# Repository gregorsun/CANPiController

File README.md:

# CANPiController

**CAN** **Pi**c **Controller** a CAN 2.0 B or CAN FD Controller board with the [PIC18F27Q84](https://www.microchip.com/wwwproducts/en/PIC18F27Q84) controller and the [ATA65620](https://www.microchip.com/wwwproducts/en/ATA6560) CAN Transeiver.

This example project showcases the setup and use of the new CAN FD module in CAN 2.0 mode on the PIC18-Q84 family of devices with the CANPiController board.The code periodically transmits CAN frames on a 1 second interval until receiving a specific message (modeled after OBD II), then will respond to certain queries with built-in data.
These examples is the CAN implementation of the CAN FD example of [pic18F57q84-curiosity-nano-CAN-node-mplab-mcc](https://github.com/microchip-pic-avr-examples/pic18F57q84-curiosity-nano-CAN-node-mplab-mcc) from @MicrochipTech

## Related Documentation

- Basic Configuration of the CAN FD Module Technical Brief [(ww1.microchip.com/downloads/en/Appnotes/90003266A.pdf)](https://ww1.microchip.com/downloads/en/Appnotes/90003266A.pdf)
- PIC18F27/47/57Q84 Datasheet [(https://www.microchip.com/wwwproducts/en/PIC18F57Q84)](https://www.microchip.com/wwwproducts/en/PIC18F57Q84)

## Software Used

- MPLAB® X IDE 5.50 or newer [(microchip.com/mplab/mplab-x-ide)](http://www.microchip.com/mplab/mplab-x-ide)
- MPLAB® XC8 2.32 or a newer compiler [(microchip.com/mplab/compilers)](http://www.microchip.com/mplab/compilers)
- MPLAB® Code Configurator (MCC) 3.95.0 or newer [(microchip.com/mplab/mplab-code-configurator)](https://www.microchip.com/mplab/mplab-code-configurator)
- MPLAB® Code Configurator (MCC) Device Libraries PIC10 / PIC12 / PIC16 / PIC18 MCUs 1.81.7 or newer [(microchip.com/mplab/mplab-code-configurator)](https://www.microchip.com/mplab/mplab-code-configurator)
- Microchip PIC18F-Q Series Device Support (1.11.185) or newer [(packs.download.microchip.com/)](https://packs.download.microchip.com/)

## Hardware Used

Hardware Used

- [*KiCAD* project files](https://github.com/gregorsun/CANPiController/tree/main/KiCAD)
- [README](https://github.com/gregorsun/CANPiController/blob/main/KiCAD/README.md) for the CANPiController PCB board

## Setup

The CANPiController Board is used as the development platform. In addition the [CAN BUS analyzer](https://www.microchip.com/developmenttools/productdetails/apgdt002) or any other CAN bus capable analyzer is needed to view the outgoing CAN frames and send incoming CAN frames to the device.

PIN Setup

PIN Manager Grid View

Other Setup is versy similar to the [pic18F57q84-curiosity-nano-CAN-node-mplab-mcc](https://github.com/microchip-pic-avr-examples/pic18F57q84-curiosity-nano-CAN-node-mplab-mcc)

## Changes to the Setup from the CAN FD demo

Main.c
```c

 //enable CAN Transceiver
 NSIL_SetLow();
 STBY_SetLow();
    
```

created interrupt_handler_function.h to put Interrupt handler to a seperate file
```c
/* 
 * File:   interrupt_handler_function.h
 * Author: M43998
 *
 * Created on July 1, 2021, 11:58 AM
 */

#ifndef INTERRUPT_HANDLER_FUNCTION_H
#define	INTERRUPT_HANDLER_FUNCTION_H

#ifdef	__cplusplus
extern "C" {
#endif

void TU16A__C1_TransmitInterruptHandler(void);
void C1__ReceiveFIFO1NotEmptyHandler(void);

#ifdef	__cplusplus
}
#endif

#endif	/* INTERRUPT_HANDLER_FUNCTION_H */
```

interrupt_handler_function.c
- The Universal timer is used for a 1 second "heartbeat" periodic transmission to ensure that the hardware is properly connected and programmed.  This periodic transmission's code is within the Universal Timer 1A's interrupt routine:
- The CAN is set up to interrupt when the receive FIFO is not empty.  The logic for processing and handling incoming messages is placed within this interrupt.
- The CAN_MSG_OBJ has to be set up as CAN message and not as a CAN FD message!

```c
/**
 Interrupt Handler function

  @author
 * Gregor Sunderdiek

  @File Name
    interrupt_handler_function.c

  @Summary
    Interrupt function handler for CAn and TU16a, so that MCC does not overide the DefaultInterruptHandler in the tu16a.c
 * TU16A_DefaultInterruptHandler has to be disabled in tu16a.c
 
 change in tua16.c
 * // Set Default Interrupt Handler
    TU16A_SetInterruptHandler(TU16A_C1_TransmitInterruptHandler);
 changes in can1.
 * //CAN1_SetFIFO1NotEmptyHandler(DefaultFIFO1NotEmptyHandler);
    CAN1_SetFIFO1NotEmptyHandler(C1__ReceiveFIFO1NotEmptyHandler);
 * 
*/

#include <xc.h>
#include "interrupt_handler_function.h"
#include "mcc_generated_files/can1.h"
#include "mcc_generated_files/tu16a.h"

void TU16A__C1_TransmitInterruptHandler(void){
    CAN_MSG_OBJ Transmission;
    uint8_t Transmit_Data[8]={0x00,0x11,0x22,0x33,0x44,0x55,0x66,0x77};
    __debug_break();
    Transmission.field.brs=CAN_NON_BRS_MODE;
    Transmission.field.dlc=DLC_8;
    Transmission.field.formatType=CAN_2_0_FORMAT;
    Transmission.field.frameType=CAN_FRAME_DATA;
    Transmission.field.idType=CAN_FRAME_STD;
    Transmission.msgId=0x585;
    Transmission.data=Transmit_Data;
    if(CAN_TX_FIFO_AVAILABLE == (CAN1_TransmitFIFOStatusGet(TXQ) & CAN_TX_FIFO_AVAILABLE))
                {
                    CAN1_Transmit(TXQ, &Transmission);
                }
} // end void TU16A_DefaultInterruptHandler(void)

void C1__ReceiveFIFO1NotEmptyHandler(void){
    TU16ACON0bits.ON = 0;  //stop the periodic heartbeat, go into response mode
    CAN_MSG_OBJ Currently_Processing;
    CAN_MSG_OBJ Return_Message;
    uint8_t data_Out[8];
    uint8_t mode=0;
    uint8_t PID=0;
    uint8_t numBytes=0;
    while(1)
    {
        if(CAN1_ReceivedMessageCountGet() > 0) 
        {
            if(true == CAN1_ReceiveFrom(FIFO1,&Currently_Processing)) //receive the message
            {
                break;
            }
        }
    }
    numBytes=Currently_Processing.data[0];
    mode=Currently_Processing.data[1];
    PID=Currently_Processing.data[2];
    Return_Message.msgId=0x7E;
    Return_Message.field.dlc=8;
    Return_Message.field.brs=CAN_NON_BRS_MODE;
    Return_Message.field.idType=CAN_FRAME_STD;
    Return_Message.field.formatType=CAN_2_0_FORMAT;
    Return_Message.field.frameType=CAN_FRAME_DATA;
    data_Out[1]=mode+0x40;
    data_Out[2]=PID;
    data_Out[7]=0x55; //00h or 55h recommended by SAE standard
    if (mode!=0x01||numBytes!=2)  //only respond with current data and a SAE standard broadcast request with 2 following bytes
    {
        return;
    }
    
    else if (PID==0x00)  //PIDs supported
    {
        data_Out[0]=6;
        data_Out[3]=0x18;  //supports engine load, coolant temp
        data_Out[4]=0x78;  //supports fuel pressure, intake pressure, engine speed, vehicle speed
        data_Out[5]=0x00;
        data_Out[6]=0x00;  //no more supported PIDs
        
    }
    
    else if (PID==0x04) //Engine Load
    {
        data_Out[0]=3;
        data_Out[3]=191; //~75% engine load
        data_Out[4]=0x55;  
        data_Out[5]=0x55;
        data_Out[6]=0x55;  
    }

    else if (PID==0x05) //Coolant Temp
    {
        data_Out[0]=3;
        data_Out[3]=100; //60C
        data_Out[4]=0x55;  
        data_Out[5]=0x55;
        data_Out[6]=0x55; 
    }
    
    else if (PID==0x0A) //Fuel Pressure
    {
        data_Out[0]=3;
        data_Out[3]=150; //450 kPA
        data_Out[4]=0x55;  
        data_Out[5]=0x55;
        data_Out[6]=0x55; 
    }
    
    else if (PID==0x0B) //Intake Pressure
    {
        data_Out[0]=3;
        data_Out[3]=200; //200 kPA
        data_Out[4]=0x55;  
        data_Out[5]=0x55;
        data_Out[6]=0x55; 
    }
    
    else if (PID==0x0C) //Engine Speed
    {
        data_Out[0]=4;
        data_Out[3]=54;    //256A+B/4=3500 RPM
        data_Out[4]=176; 
        data_Out[5]=0x55;
        data_Out[6]=0x55; 
    }
    
    else if (PID==0x0D) //Vehicle Speed
    {
        data_Out[0]=3;
        data_Out[3]=70;  //70 km/h
        data_Out[4]=0x55;  
        data_Out[5]=0x55;
        data_Out[6]=0x55; 
    }
    
    else if (PID==0xFF) //go back to heartbeat mode
    {
        TU16ACON0bits.ON = 1;  //stop the response mode, go into periodic heartbeat
        return;
    }
        Return_Message.data=data_Out; 
        if(CAN_TX_FIFO_AVAILABLE == (CAN1_TransmitFIFOStatusGet(TXQ) & CAN_TX_FIFO_AVAILABLE))
        {
            CAN1_Transmit(TXQ, &Return_Message);
        }
        return;

} // end 
```

## Operation

On Power-up, the code will periodically transmit messages 

However, upon receiving a message with the CAN ID of 0x7DF, it will cease the periodic messages and go into response mode.  In this mode it will respond to specific messages, as shown below:

After sending a message with 0xFF in the third data byte while in response mode, the node will return to periodic mode and begin sending periodic messages again.

## Summary

This Demo gives an example of hardware and software setup for a basic CAN node with both periodic and response-driven transmissions, showcasing baud rate setup, message filtering, and RX and TX setup.  

##Debug with MLPAB PICkit4

The PCB connector J3 has not the same connection as the [PICkit4 Debugger](https://www.microchip.com/DevelopmentTools/ProductDetails/PartNO/PG164140)

A cable with soldering with connector is needed to match the PICkit4

with the CANPiController board ICSP Interface J3

PICkit4 Header
| PICkit4       |
| ------------- | 
| 1. VPP/MCLR   |
| 2. VDD        |
| 3. VSS        | 
| 4. PGD        | 
| 5. PGC        | 
| 6. NC         | 

ICSP Header J3 on the CANPIController
| ICSP J3       |
| ------------- |
| 1. MCLR VPP   |
| 2. +5V VDD    |
| 3. ICSPDAT    |
| 4. ICSPCLK    |
| 5. NC         |
| 6. GND        |

Connection from the PICkit4 Header to the ICSP Header J3 on the CANPIController
| PICkit4       | ICSP J3       |
| ------------- | ------------- |
| 1. VPP/MCLR   | 1. MCLR VPP   |
| 2. VDD        | 2. +5V VDD    |
| 3. VSS        | 6. GND        |
| 4. PGD        | 3. ICSPDAT    |
| 5. PGC        | 5. NC         |
| 6. NC         | 4. ICSPCLK    |

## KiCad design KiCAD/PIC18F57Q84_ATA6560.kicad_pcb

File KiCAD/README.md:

**KiCAD project file for the CANPicontroller ver1**
*Main components*
1. Semiconductors
  - U1 - [PIC18F27Q84-ISS](https://www.microchip.com/wwwproducts/en/PIC18F27Q84) for CAN-FD or [PIC18F27Q83-ISS](https://www.microchip.com/wwwproducts/en/PIC18F27Q83) for CAN 2.0V 
  - U2 - CAN Transceiver - [ATA6560](https://www.microchip.com/wwwproducts/en/ATA6560)
2. Electromechanical
  - J1 - USB-C for +5V only
  - J2 - Header for USB-C
  - J3 - [ICSP-Header](https://ww1.microchip.com/downloads/en/devicedoc/30277d.pdf)
  - J4 - Header for signals CANH, CANL and GND
  - J5 and J6 Header - Curiosity Nano Debug Header
    - You have to use a [PIC18F57Q84 Curiosity Nano](https://ww1.microchip.com/downloads/en/DeviceDoc/PIC18F57Q84-Curiosity-Nano-Hardware-User-Guide-DS50003011.pdf)
    - Only the  Curiosity Nano Standard Pinout Pins are needed
    - 
  - J7 Header - signal to/from CAN Transceiver
  - J8 and J9 - [Mikroelektonika click header](https://www.mikroe.com/click-boards)
  - J10 - DB9 male connector for CAN connection

*WARNING*
- Only connect one power supply to the board, Either power the board via USB, the ICSP header or the PIC18F-Q84 Curiosity Nano header

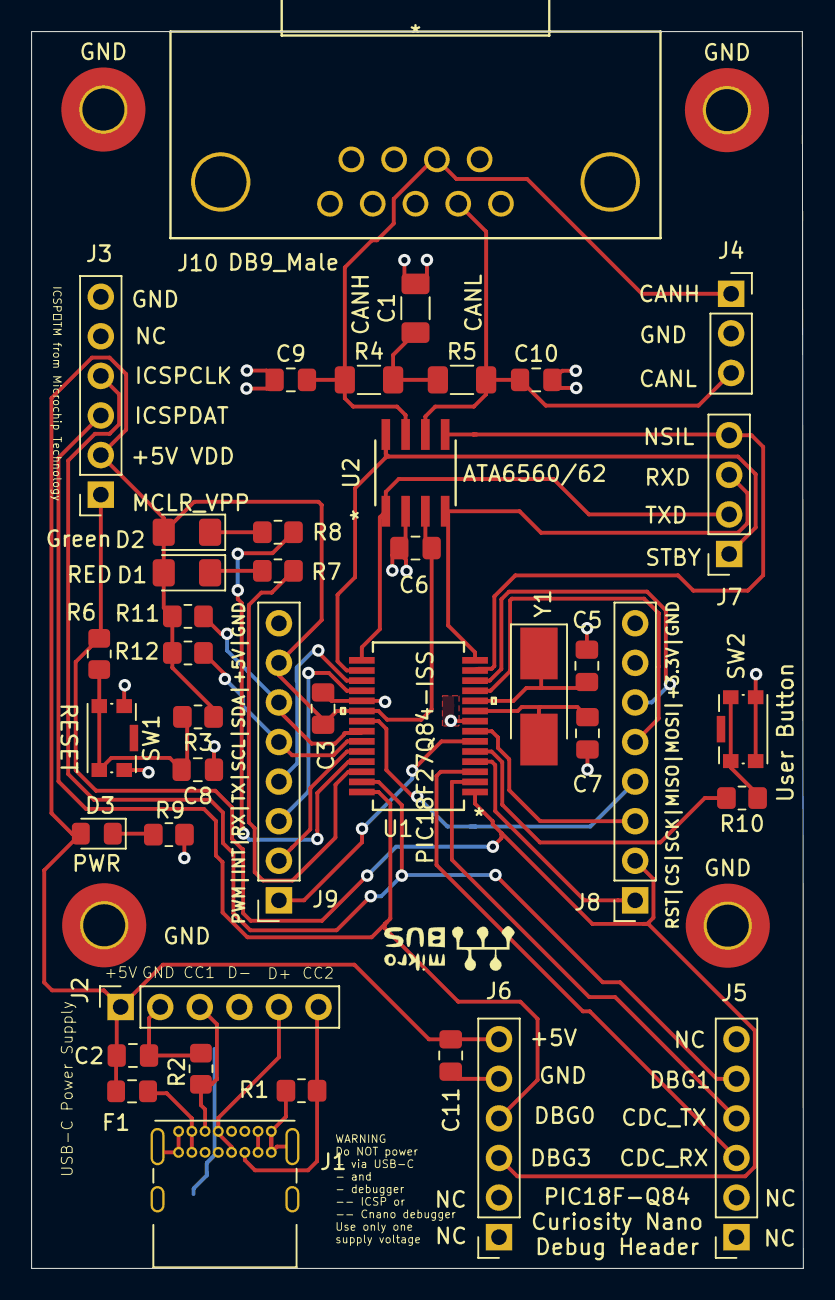
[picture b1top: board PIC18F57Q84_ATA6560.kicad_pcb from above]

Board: 2 copper layers, 49.5 x 79.4 mm, 45 parts (0 on the bottom side), 40 nets.

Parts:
C1: 4.7n/50V; C_1206_3216Metric_Pad1.33x1.80mm_HandSolder
C2, C11: 2.2u; C_0805_2012Metric_Pad1.18x1.45mm_HandSolder
C3, C6: 100n; C_0805_2012Metric_Pad1.18x1.45mm_HandSolder
C5, C7: 26p; C_0805_2012Metric_Pad1.18x1.45mm_HandSolder
C8: 0.1u; C_0805_2012Metric_Pad1.18x1.45mm_HandSolder
C9, C10: 100p/50V; C_0805_2012Metric_Pad1.18x1.45mm_HandSolder
D1: RED; LED_1206_3216Metric_Pad1.42x1.75mm_HandSolder
D2: Green; LED_1206_3216Metric_Pad1.42x1.75mm_HandSolder
D3: Yellow; LED_0805_2012Metric_Pad1.15x1.40mm_HandSolder
F1: Fuse MC36213; Fuse_0805_2012Metric_Pad1.15x1.40mm_HandSolder
GND: MountingHole_2.7mm_M2.5_Pad_TopBottom
GND#2, GND#3, GND#4: MountingHole_2.7mm_M2.5_Pad_TopBottom
J1: USB_C_Receptacle_USB2.0; USB_C_Receptacle_GCT_USB4085
J2, J3, J5, J6: Conn_01x06; PinSocket_1x06_P2.54mm_Vertical
J4: Conn_01x03; PinSocket_1x03_P2.54mm_Vertical
J7: Conn_01x04; PinSocket_1x04_P2.54mm_Vertical
J8, J9: Conn_01x08; PinSocket_1x08_P2.54mm_Vertical
J10: DB9_Male; 5747840-4
R1, R2: 5.1k; R_0805_2012Metric_Pad1.20x1.40mm_HandSolder
R3, R11, R12: 10k; R_0805_2012Metric_Pad1.20x1.40mm_HandSolder
R4, R5: 60R/0.5W; R_1206_3216Metric_Pad1.30x1.75mm_HandSolder
R6: 470R; R_0805_2012Metric_Pad1.20x1.40mm_HandSolder
R7, R8, R9, R10: 1k; R_0805_2012Metric_Pad1.20x1.40mm_HandSolder
SW1, SW2: SW_Push; SW_Push_1P1T-SH_NO_CK_KMR2xxG
U1: PIC18F27Q84-ISS; PIC18F27Q43-I&slash_SS
U2: ATA6560/62; ATA6561-GAQW-N
Y1: Crystal 10MHz, ABM3-10.0000MHZ-D2Y-T; Crystal_SMD_Abracon_ABM3-2Pin_5.0x3.2mm_HandSoldering

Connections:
CDC_RX: J5.3, U1.3
CDC_TX: J5.4, U1.2
DBG0: J3.3, J6.4, U1.28
DBG1: J3.4, J5.5, U1.27
DBG3: J3.1, J6.3, J8.2, R6.1, U1.1
GND: C1.2, C2.2, C3.2, C5.1, C6.1, C7.2, C8.2, C9.1, C10.2, C11.2, GND.1, GND#2.1, GND#3.1, GND#4.1, J1.A1, J1.A12, J1.B1, J1.B12, J1.S1, J2.2, J3.6, J4.2, J6.5, J8.8, J9.8, J10.3, R1.2, R2.2, R9.2, SW1.1, SW2.2, U1.8, U1.19, U2.2
NSIL: J7.4, U1.13, U2.5
unnamed: C1.1, R4.2, R5.1
unnamed: C8.1, R3.2, R6.2, SW1.2
unnamed: C9.2, J4.1, J10.7, R4.1, U2.7
unnamed: C10.1, J4.3, J10.2, R5.2, U2.6
unnamed: D1.1, R7.1
unnamed: D2.1, R8.1
unnamed: D3.1, R9.1
unnamed: F1.2, J1.A4, J1.A9, J1.B4, J1.B9
unnamed: J1.A5, J2.3, R2.1
unnamed: J1.A6, J1.B6, J2.5
unnamed: J1.A7, J1.B7, J2.4
unnamed: J1.B5, J2.6, R1.1
unnamed: R10.1, SW2.1
OSC1: C5.2, U1.10, Y1.1
OSC2: C7.1, U1.9, Y1.2
RA2_A0: J8.1, U1.4
RA3_SW2: R10.2, U1.5
RA4_PWM: J9.1, U1.6
RA5_CS: J8.3, U1.7
RB0_SCK: J8.4, U1.21
RB1_SDA: J9.6, R11.2, U1.22
RB2_SCL: J9.5, R12.2, U1.23
RB3_INT: J9.2, U1.24
RB4_LED_GREEN: R8.2, U1.25
RB5_LED_RED: R7.2, U1.26
RC0_MISO: J8.5, U1.11
RC1_MOSI: J8.6, U1.12
RC6_TX: J9.4, U1.17
RC7_RX: J9.3, U1.18
RXD: J7.3, U1.14, U2.4
STBY: J7.1, U1.16, U2.8
TXD: J7.2, U1.15, U2.1
VTG: C2.1, C3.1, C6.2, C11.1, D1.2, D2.2, D3.2, F1.1, J2.1, J3.2, J6.6, J9.7, R3.1, R11.1, R12.1, U1.20, U2.3

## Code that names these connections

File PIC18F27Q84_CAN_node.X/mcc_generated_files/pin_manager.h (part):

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// get/set IO_RB4_LED_GREEN aliases
#define IO_RB4_LED_GREEN_TRIS                 TRISBbits.TRISB4
#define IO_RB4_LED_GREEN_LAT                  LATBbits.LATB4
#define IO_RB4_LED_GREEN_PORT                 PORTBbits.RB4
#define IO_RB4_LED_GREEN_WPU                  WPUBbits.WPUB4
#define IO_RB4_LED_GREEN_OD                   ODCONBbits.ODCB4
#define IO_RB4_LED_GREEN_ANS                  ANSELBbits.ANSELB4
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// get/set IO_RB5_LED_RED aliases
#define IO_RB5_LED_RED_TRIS                 TRISBbits.TRISB5
#define IO_RB5_LED_RED_LAT                  LATBbits.LATB5
#define IO_RB5_LED_RED_PORT                 PORTBbits.RB5
#define IO_RB5_LED_RED_WPU                  WPUBbits.WPUB5
#define IO_RB5_LED_RED_OD                   ODCONBbits.ODCB5
#define IO_RB5_LED_RED_ANS                  ANSELBbits.ANSELB5
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// get/set NSIL aliases
#define NSIL_TRIS                 TRISCbits.TRISC2
#define NSIL_LAT                  LATCbits.LATC2
#define NSIL_PORT                 PORTCbits.RC2
#define NSIL_WPU                  WPUCbits.WPUC2
#define NSIL_OD                   ODCONCbits.ODCC2
#define NSIL_ANS                  ANSELCbits.ANSELC2
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// get/set STBY aliases
#define STBY_TRIS                 TRISCbits.TRISC5
#define STBY_LAT                  LATCbits.LATC5
#define STBY_PORT                 PORTCbits.RC5
#define STBY_WPU                  WPUCbits.WPUC5
#define STBY_OD                   ODCONCbits.ODCC5
#define STBY_ANS                  ANSELCbits.ANSELC5
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
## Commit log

2021-07-02 Create Images
2021-07-02 Initial commit
    Tested with CAN BUS Analyzer
2021-07-02 Update readme file with code explanation
2021-07-02 Update README.md
    explanation about SW project MPLAB X and debugger connection

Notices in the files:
PIC18F27Q84_CAN_node.X/mcc_generated_files/pin_manager.h:
(c) 2018 Microchip Technology Inc. and its subsidiaries.
parts and their libraries:
Copyright 2016 Accelerated Designs. All rights reserved.
